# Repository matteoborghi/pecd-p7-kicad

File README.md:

# PECD P7: SiC traction inverter board (KiCad)

KiCad project of the board behind the report
[pecd-p7-report](https://github.com/matteoborghi/pecd-p7-report): a
three-phase two-level SiC traction inverter, 800 V DC link, 30 A rms per
phase, 20 kHz. The board is 6 layers, 1.6 mm thick, revision 1.2.

The report covers only the power stage. On the PCB it is the area marked
with a dashed box and a name on layer `User.1`.

## Schematic

The root sheet `PECD_P7.kicad_sch` has six hierarchical sheets:

| Sheet | Content |
|---|---|
| `1_power_stage` | six SiC MOSFETs (E3M0016120K), DC-link capacitors, shunts, DC and phase terminals |
| `2_gate_drive` | isolated gate drivers |
| `3_phase_sense` | current and voltage measurement |
| `4_aux_supply` | auxiliary supplies |
| `5_control_if` | interface to the controller |
| `6_dclink_mgmt` | DC-link management |

`leg.kicad_sch` is the half-bridge used three times in the power stage.
`drv_channel.kicad_sch` and `sense_channel.kicad_sch` are the repeated
gate-drive and measurement channels.

## Libraries

Symbols, footprints and 3D shapes of the parts that are not in the KiCad
standard libraries are in `PECD_P7.kicad_sym`, `PECD_P7.pretty` and
`PECD_P7.3dshapes`. The notes on each library file (in Italian) are in
`librerie/NOTE_librerie.md`.

## Tags

- `pcb-v1.0`, `pcb-v1.1`, `pcb-v1.2`: board revisions.
- `exam-v1`: board with the power-stage box used by the report.

The default branch is `for-exam`, which adds the power-stage box to `main`.

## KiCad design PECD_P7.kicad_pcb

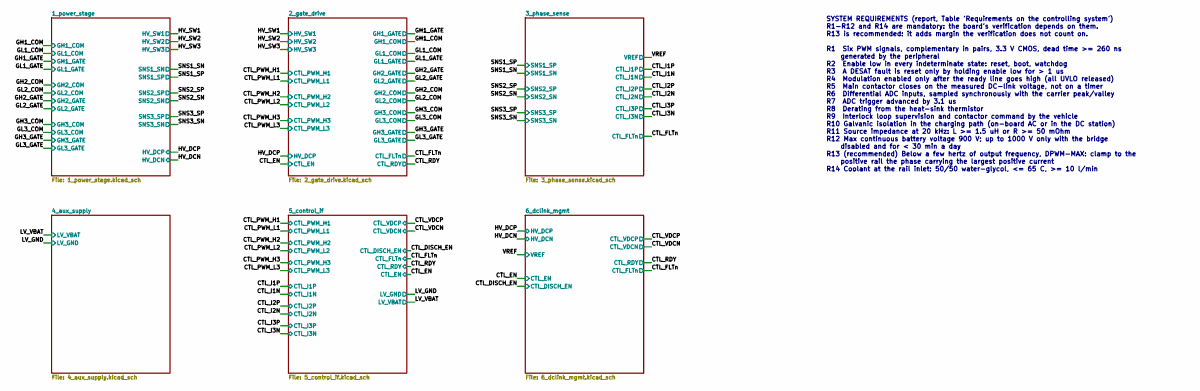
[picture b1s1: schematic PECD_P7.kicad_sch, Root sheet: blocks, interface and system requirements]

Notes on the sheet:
SYSTEM REQUIREMENTS (report, Table 'Requirements on the controlling system') R1-R12 and R14 are mandatory: the board's verification depends on them. R13 is recommended: it adds margin the verification does not count on. R1 Six PWM signals, complementary in pairs, 3.3 V CMOS, dead time >= 260 ns gen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

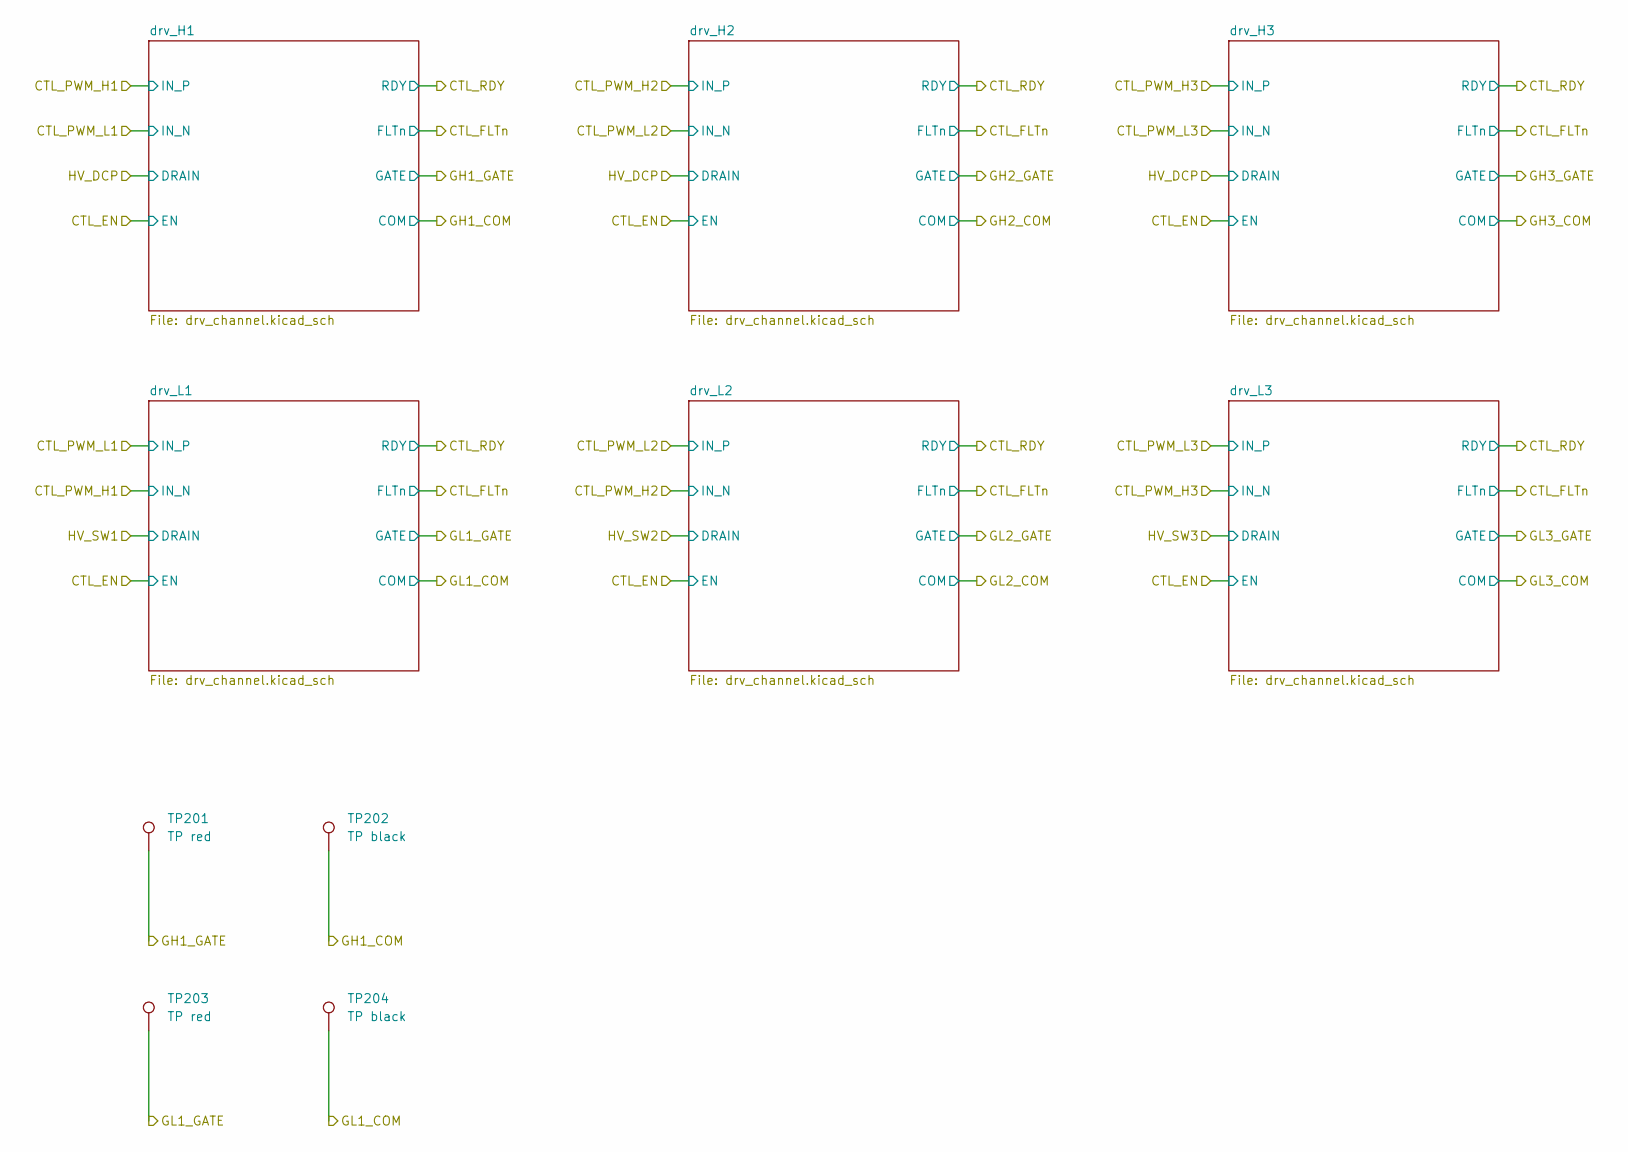
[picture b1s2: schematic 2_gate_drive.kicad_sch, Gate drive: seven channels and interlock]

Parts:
TP201, TP203: TP red; TestPoint_Keystone_5000-5004_Miniature; MPN 5000
TP202, TP204: TP black; TestPoint_Keystone_5000-5004_Miniature; MPN 5001

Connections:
/GH1_COM: TP202.1 (1_1); also elsewhere on the board
/GH1_GATE: TP201.1 (1_1); also elsewhere on the board
/GL1_COM: TP204.1 (1_1); also elsewhere on the board
/GL1_GATE: TP203.1 (1_1); also elsewhere on the board

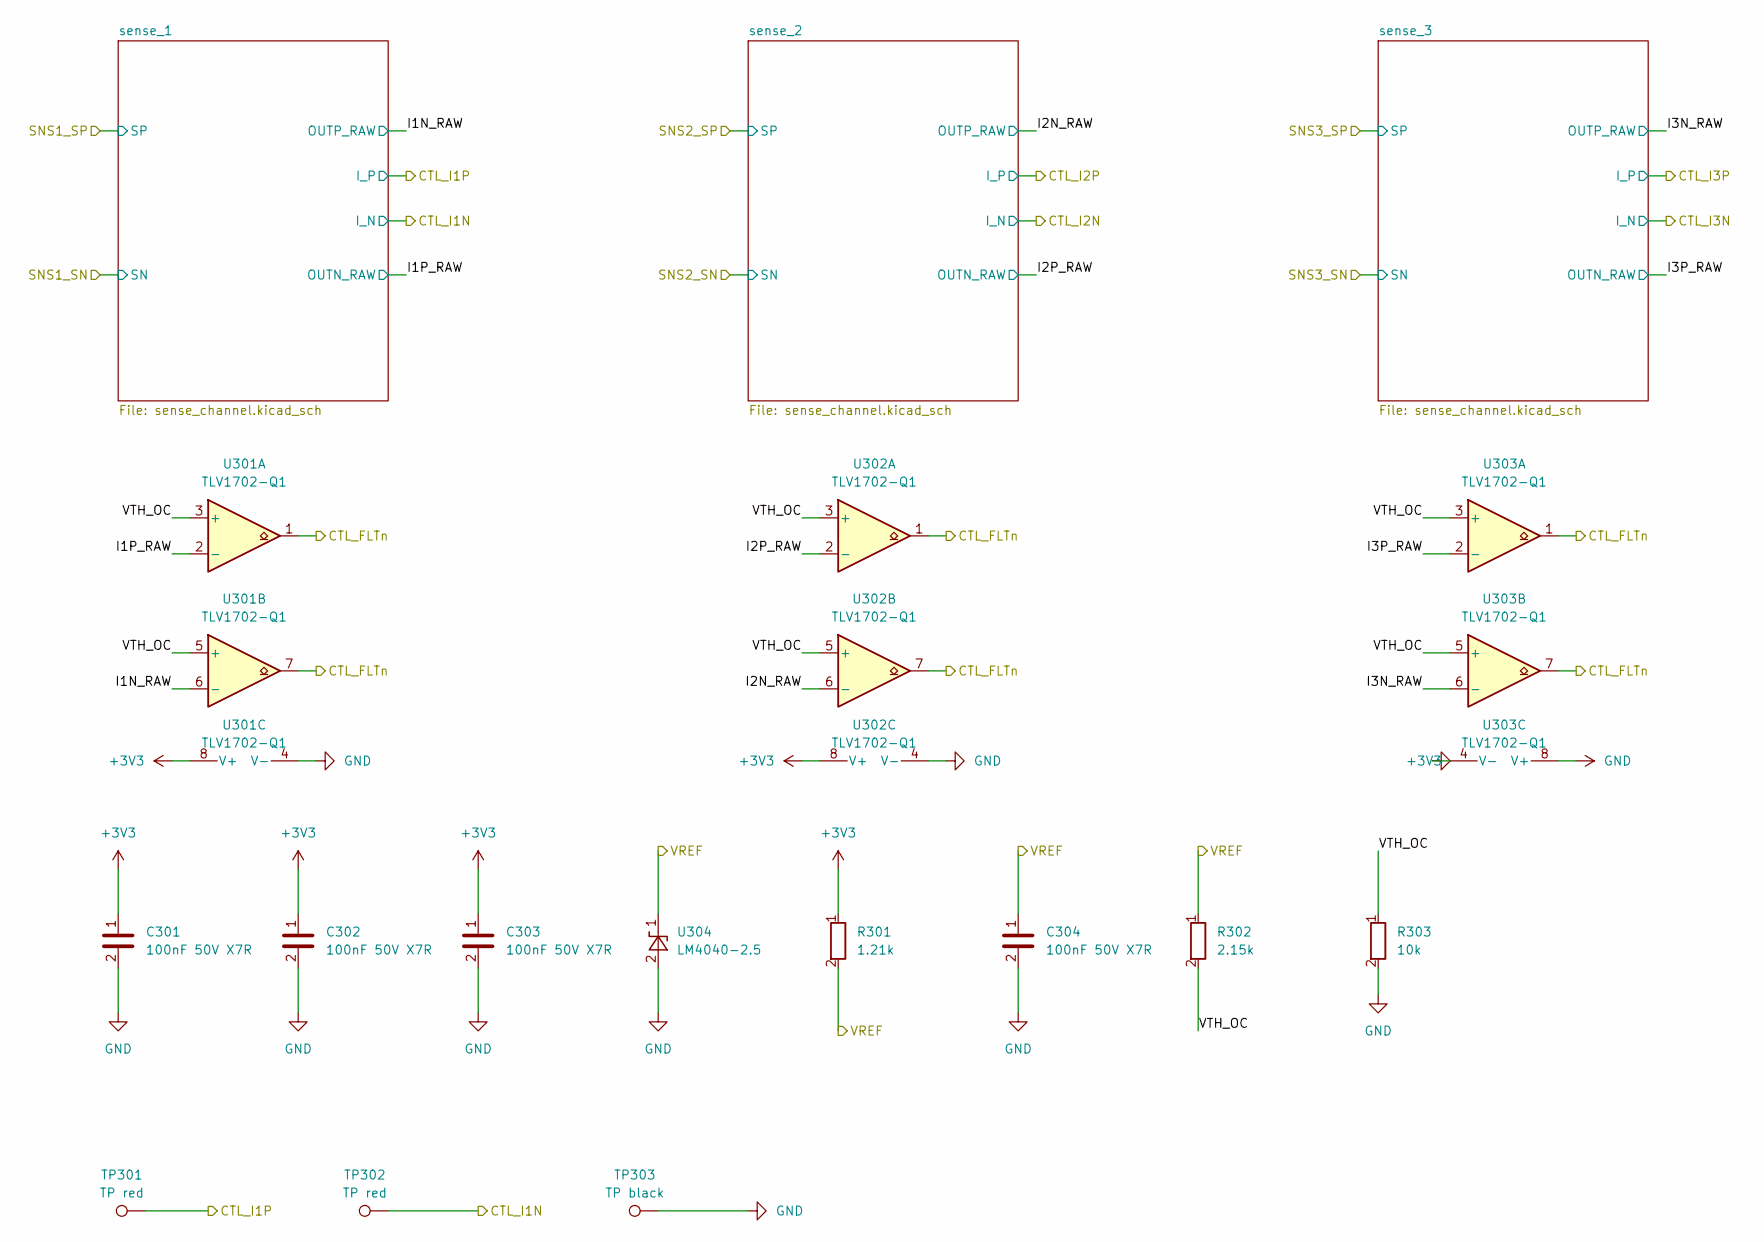
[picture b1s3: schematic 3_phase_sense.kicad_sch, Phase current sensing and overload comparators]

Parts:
C301, C302, C303, C304: 100nF 50V X7R; C_0603_1608Metric; MPN GCM188R71H104KA57D
R301: 1.21k; R_0603_1608Metric; MPN ERJ-3EKF1211V
R302: 2.15k; R_0603_1608Metric; MPN ERJ-3EKF2151V
R303: 10k; R_0603_1608Metric; MPN ERJ-3EKF1002V
TP301, TP302: TP red; TestPoint_Keystone_5000-5004_Miniature; MPN 5000
TP303: TP black; TestPoint_Keystone_5000-5004_Miniature; MPN 5001
U301, U302, U303: TLV1702-Q1; VSSOP-8_3x3mm_P0.65mm; MPN TLV1702AQDGKRQ1
U304: LM4040-2.5; SOT-23; MPN LM4040QBIM3-2.5/NOPB

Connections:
+3V3: C301.1, C302.1, C303.1, R301.1, U301.8 (V+), U302.8 (V+), U303.8 (V+); also elsewhere on the board
/3_phase_sense/I1N_RAW: U301.6 (-); also elsewhere on the board
/3_phase_sense/I1P_RAW: U301.2 (-); also elsewhere on the board
/3_phase_sense/I2N_RAW: U302.6 (-); also elsewhere on the board
/3_phase_sense/I2P_RAW: U302.2 (-); also elsewhere on the board
/3_phase_sense/I3N_RAW: U303.6 (-); also elsewhere on the board
/3_phase_sense/I3P_RAW: U303.2 (-); also elsewhere on the board
/3_phase_sense/VTH_OC: R302.2, R303.1, U301.3 (+), U301.5 (+), U302.3 (+), U302.5 (+), U303.3 (+), U303.5 (+)
/CTL_FLTn: U301.1, U301.7, U302.1, U302.7, U303.1, U303.7; also elsewhere on the board
/CTL_I1N: TP302.1 (1_1); also elsewhere on the board
/CTL_I1P: TP301.1 (1_1); also elsewhere on the board
/VREF: C304.1, R301.2, R302.1, U304.1 (K); also elsewhere on the board
GND: C301.2, C302.2, C303.2, C304.2, R303.2, TP303.1 (1_1), U301.4 (V-), U302.4 (V-), U303.4 (V-), U304.2 (A); also elsewhere on the board

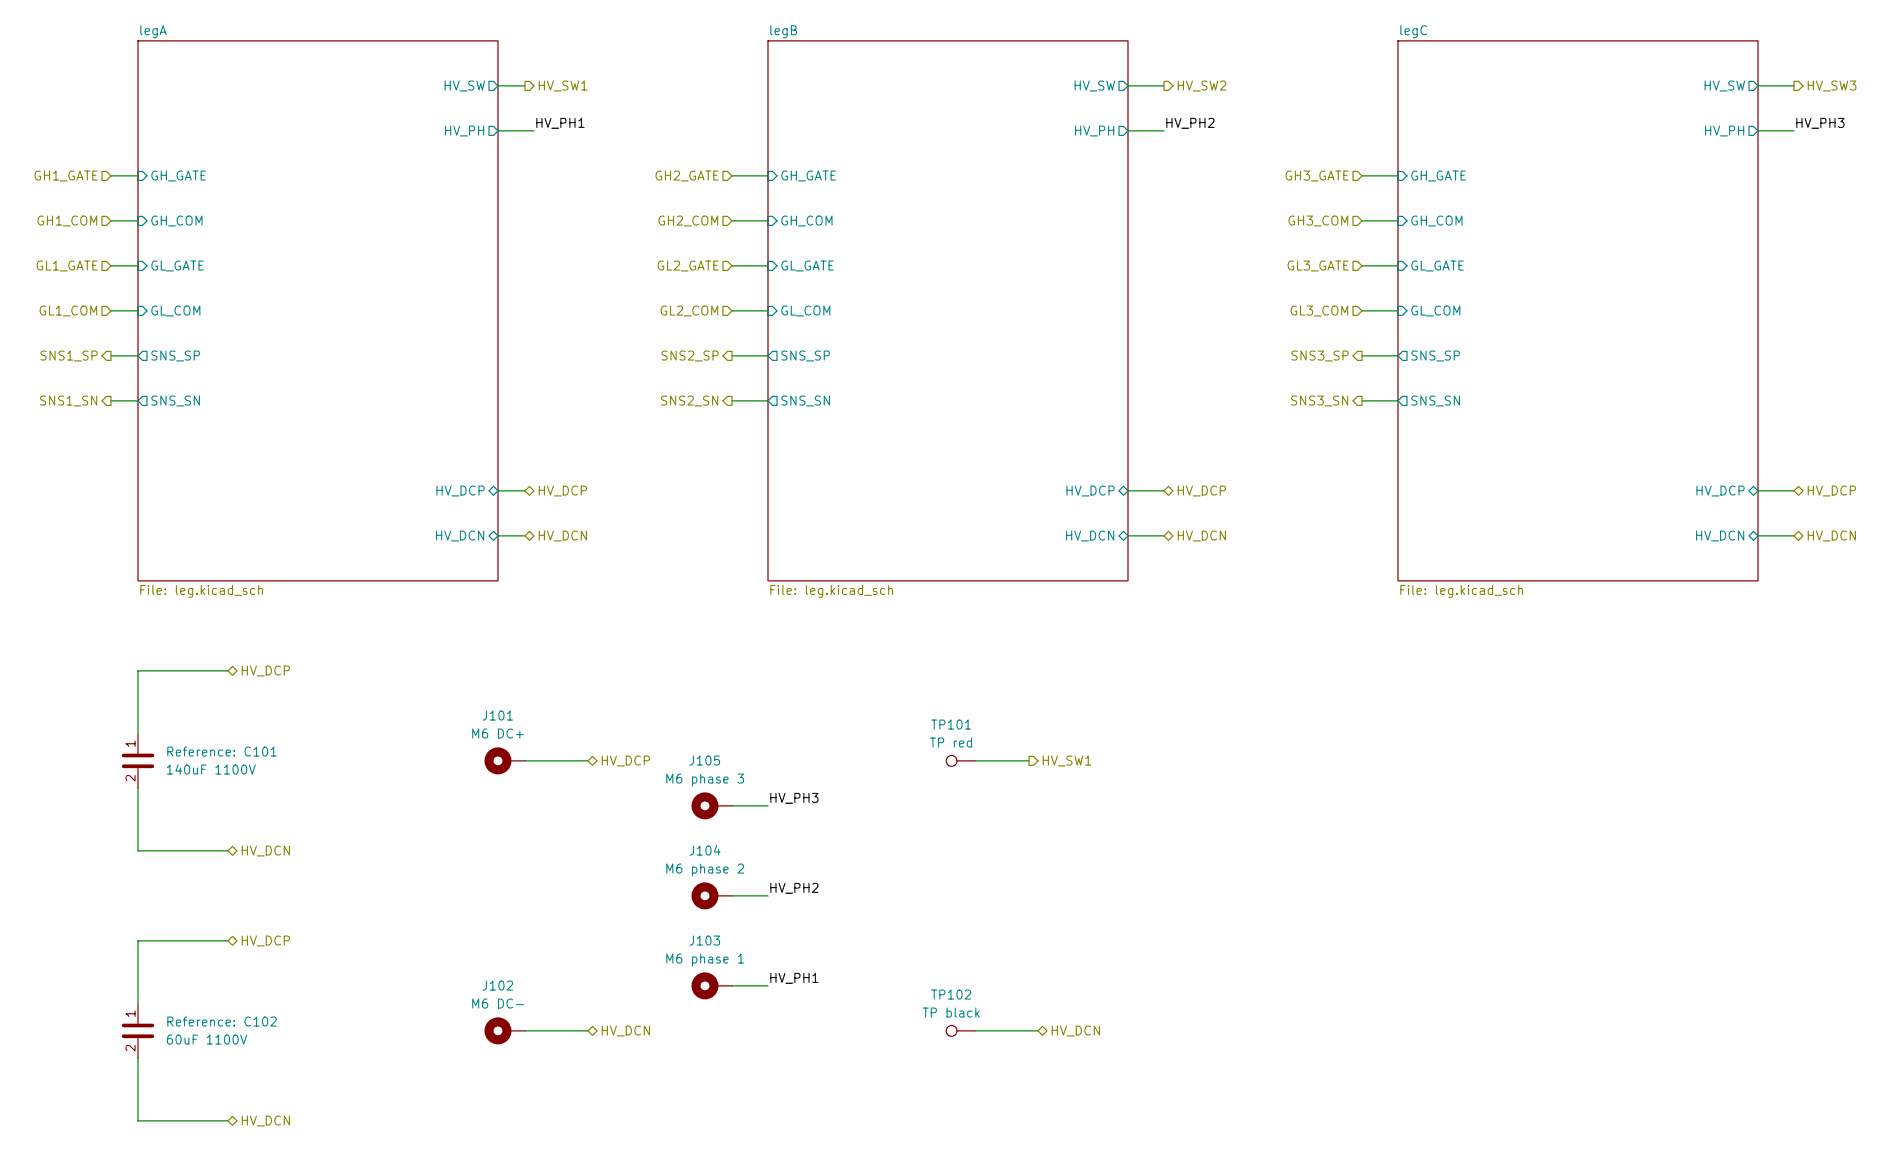
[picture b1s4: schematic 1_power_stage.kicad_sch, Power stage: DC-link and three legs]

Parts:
C101: 140uF 1100V; MKP1848_12pin_P52.5mm; MPN MKP1848714914Y5
C102: 60uF 1100V; MKP1848_6pin_P52.5mm; MPN MKP1848660914Y5
J101: M6 DC+; MountingHole_6.4mm_M6_Pad_Via
J102: M6 DC-; MountingHole_6.4mm_M6_Pad_Via
J103: M6 phase 1; MountingHole_6.4mm_M6_Pad_Via
J104: M6 phase 2; MountingHole_6.4mm_M6_Pad_Via
J105: M6 phase 3; MountingHole_6.4mm_M6_Pad_Via
TP101: TP red; TestPoint_Keystone_5000-5004_Miniature; MPN 5000
TP102: TP black; TestPoint_Keystone_5000-5004_Miniature; MPN 5001

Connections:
/1_power_stage/HV_PH1: J103.1 (1_1); also elsewhere on the board
/1_power_stage/HV_PH2: J104.1 (1_1); also elsewhere on the board
/1_power_stage/HV_PH3: J105.1 (1_1); also elsewhere on the board
/HV_DCN: C101.2, C102.2, J102.1 (1_1), TP102.1 (1_1); also elsewhere on the board
/HV_DCP: C101.1, C102.1, J101.1 (1_1); also elsewhere on the board
/HV_SW1: TP101.1 (1_1); also elsewhere on the board

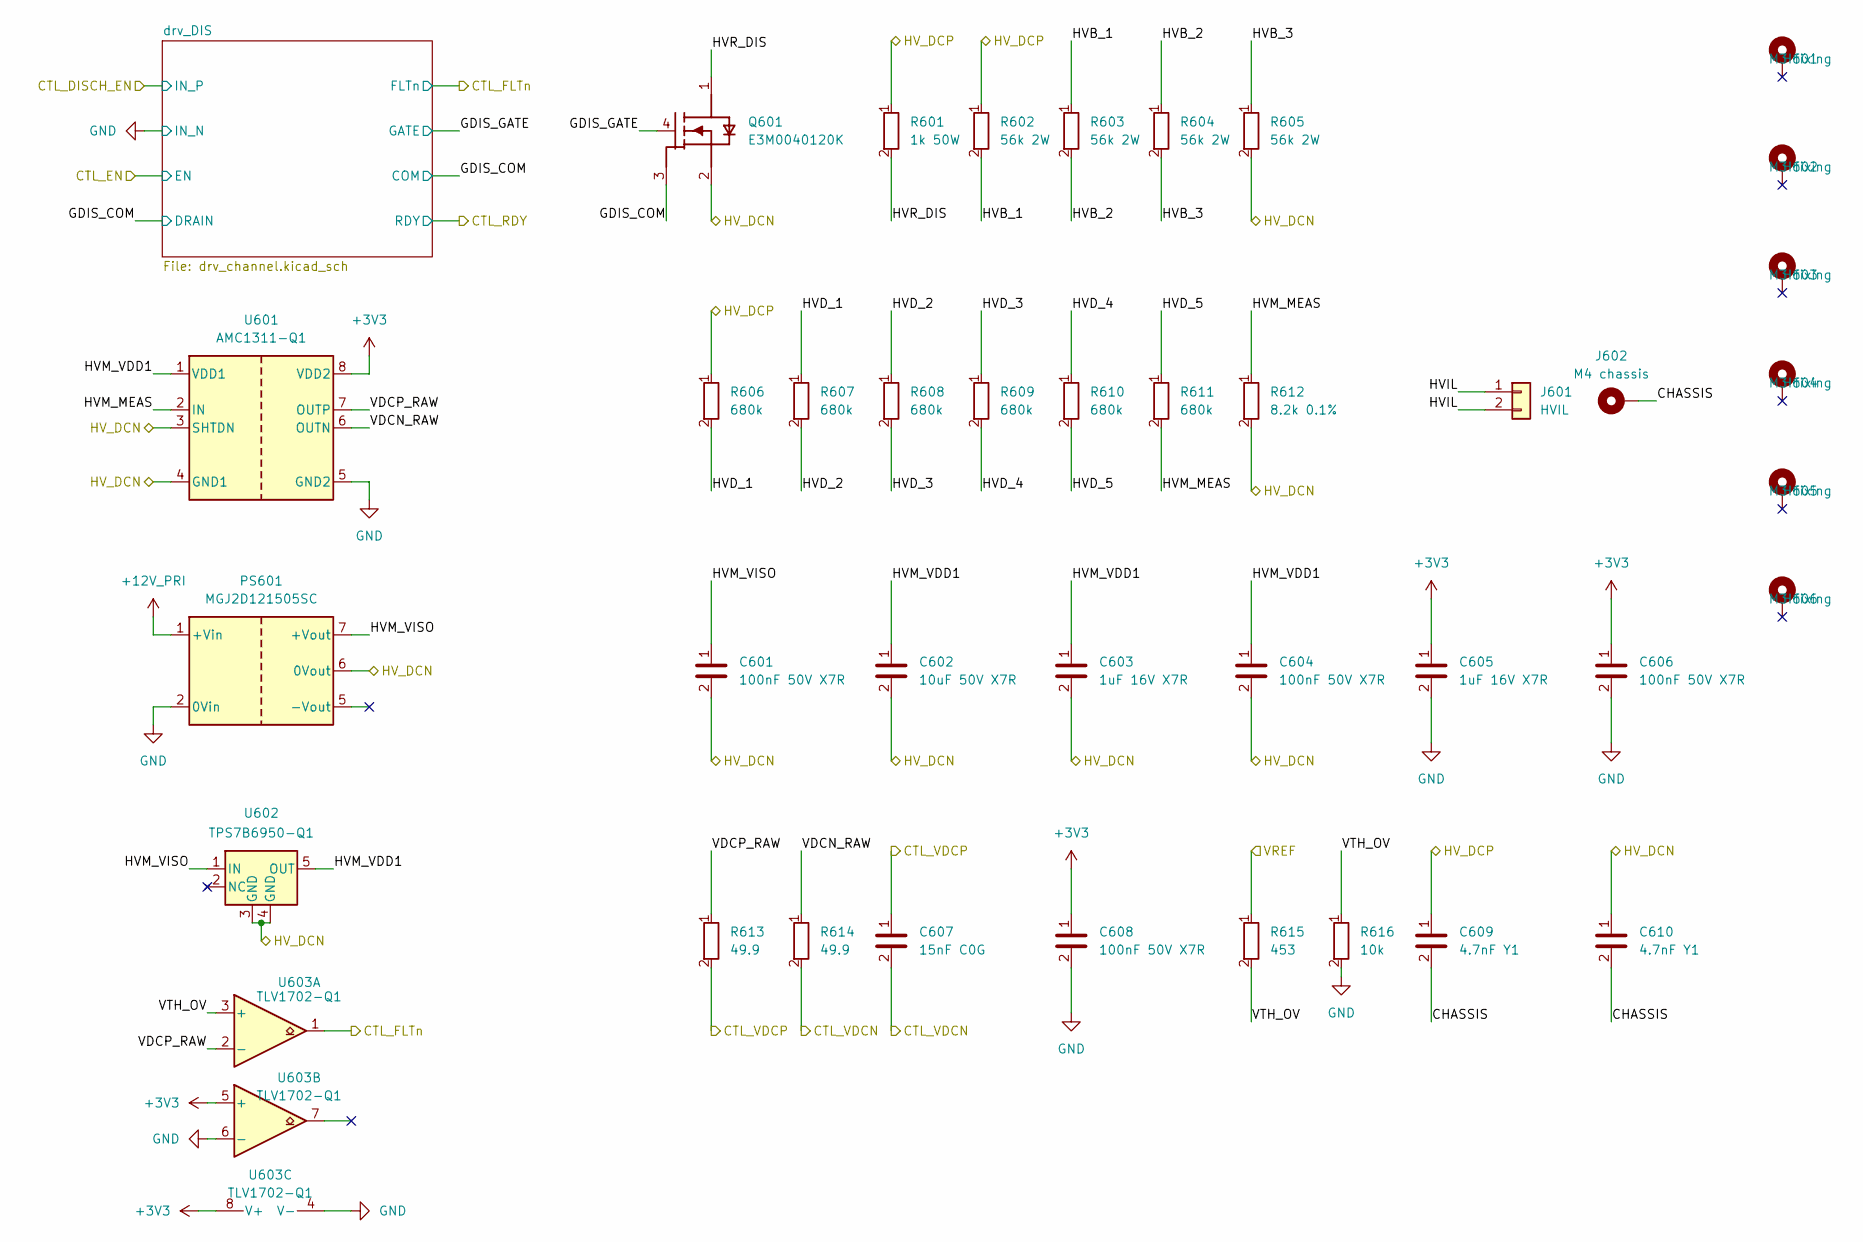
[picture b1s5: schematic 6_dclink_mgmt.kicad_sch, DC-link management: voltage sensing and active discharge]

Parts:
C601, C604, C606, C608: 100nF 50V X7R; C_0603_1608Metric; MPN GCM188R71H104KA57D
C602: 10uF 50V X7R; C_1210_3225Metric; MPN GRM32ER71H106KA12L
C603, C605: 1uF 16V X7R; C_0603_1608Metric; MPN GCM188R71C105KA64D
C607: 15nF C0G; C_0805_2012Metric; MPN GCM2195C1H153JA16D
C609, C610: 4.7nF Y1; C_Disc_Y1_D16.5_P12.5mm; MPN AY1472M65Y5UC63LX
H601, H602, H603, H604, H605, H606: M3 fixing; MountingHole_3.2mm_M3_Pad_Via
J601: HVIL; PhoenixContact_MSTBA_2,5_2-G-5,08_1x02_P5.08mm_Horizontal; MPN 1757242
J602: M4 chassis; MountingHole_4.3mm_M4_Pad_Via
PS601: MGJ2D121505SC; MGJ2_SIP7; MPN MGJ2D121505SC
Q601: E3M0040120K; TO-247-4L_Wolfspeed_Vertical; MPN E3M0040120K
R601: 1k 50W; Wire_HV_2x_P10mm; MPN HS50 1K J
R602, R603, R604, R605: 56k 2W; R_Axial_DIN0411_L9.9mm_D3.6mm_P15.24mm_Horizontal; MPN PR02000205602JR500
R606, R607, R608, R609, R610, R611: 680k; R_1206_3216Metric; MPN ERJ-8ENF6803V
R612: 8.2k 0.1%; R_1206_3216Metric; MPN ERA-3AEB822V
R613, R614: 49.9; R_0603_1608Metric; MPN ERJ-3EKF49R9V
R615: 453; R_0603_1608Metric; MPN ERJ-3EKF4530V
R616: 10k; R_0603_1608Metric; MPN ERJ-3EKF1002V
U601: AMC1311-Q1; SOIC-8W_TI_DWV_Slot; MPN AMC1311QDWVRQ1
U602: TPS7B6950-Q1; SOT-23-5; MPN TPS7B6950QDBVRQ1
U603: TLV1702-Q1; VSSOP-8_3x3mm_P0.65mm; MPN TLV1702AQDGKRQ1

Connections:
+3V3: C605.1, C606.1, C608.1, U601.8 (VDD2), U603.5 (+), U603.8 (V+); also elsewhere on the board
+12V_PRI: PS601.1 (+Vin); also elsewhere on the board
/6_dclink_mgmt/CHASSIS: C609.2, C610.2, J602.1 (1_1)
/6_dclink_mgmt/GDIS_COM: Q601.3 (S_K); also elsewhere on the board
/6_dclink_mgmt/GDIS_GATE: Q601.4 (G); also elsewhere on the board
/6_dclink_mgmt/HVB_1: R602.2, R603.1
/6_dclink_mgmt/HVB_2: R603.2, R604.1
/6_dclink_mgmt/HVB_3: R604.2, R605.1
/6_dclink_mgmt/HVD_1: R606.2, R607.1
/6_dclink_mgmt/HVD_2: R607.2, R608.1
/6_dclink_mgmt/HVD_3: R608.2, R609.1
/6_dclink_mgmt/HVD_4: R609.2, R610.1
/6_dclink_mgmt/HVD_5: R610.2, R611.1
/6_dclink_mgmt/HVIL: J601.1, J601.2
/6_dclink_mgmt/HVM_MEAS: R611.2, R612.1, U601.2 (IN)
/6_dclink_mgmt/HVM_VDD1: C602.1, C603.1, C604.1, U601.1 (VDD1), U602.5 (OUT)
/6_dclink_mgmt/HVM_VISO: C601.1, PS601.7 (+Vout), U602.1 (IN)
/6_dclink_mgmt/HVR_DIS: Q601.1 (D), R601.2
/6_dclink_mgmt/VDCN_RAW: R614.1, U601.6 (OUTN)
/6_dclink_mgmt/VDCP_RAW: R613.1, U601.7 (OUTP), U603.2 (-)
/6_dclink_mgmt/VTH_OV: R615.2, R616.1, U603.3 (+)
/CTL_FLTn: U603.1; also elsewhere on the board
/CTL_VDCN: C607.2, R614.2; also elsewhere on the board
/CTL_VDCP: C607.1, R613.2; also elsewhere on the board
/HV_DCN: C601.2, C602.2, C603.2, C604.2, C610.1, PS601.6 (0Vout), Q601.2 (S), R605.2, R612.2, U601.3 (SHTDN), U601.4 (GND1), U602.3 (GND), U602.4 (GND); also elsewhere on the board
/HV_DCP: C609.1, R601.1, R602.1, R606.1; also elsewhere on the board
/VREF: R615.1; also elsewhere on the board
GND: C605.2, C606.2, C608.2, PS601.2 (0Vin), R616.2, U601.5 (GND2), U603.4 (V-), U603.6 (-); also elsewhere on the board

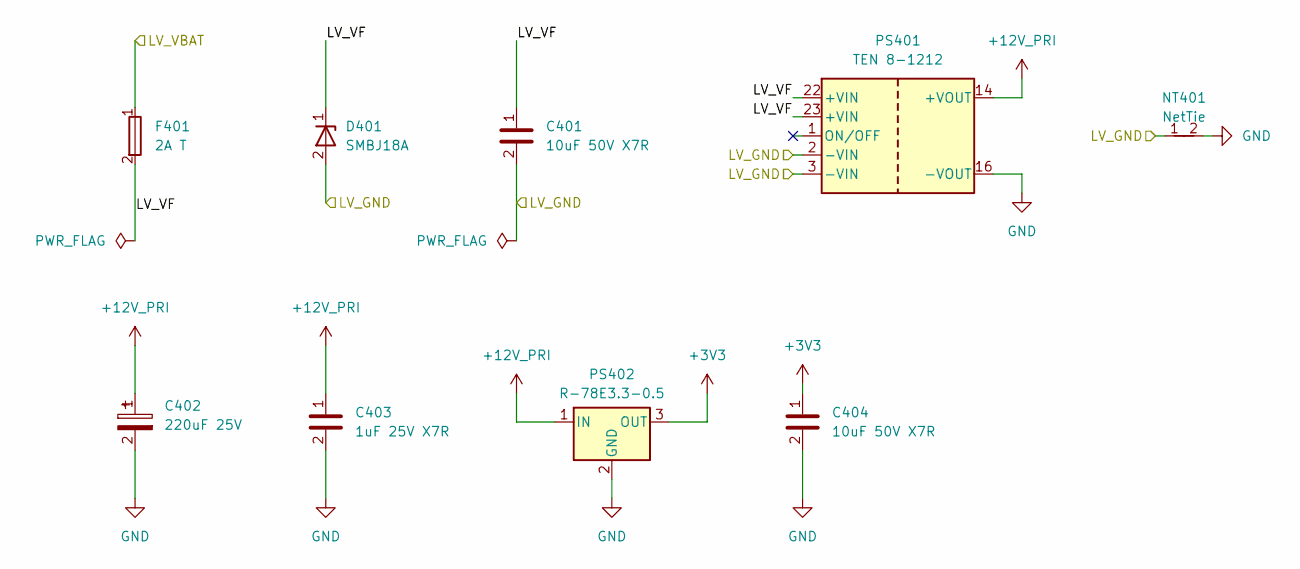
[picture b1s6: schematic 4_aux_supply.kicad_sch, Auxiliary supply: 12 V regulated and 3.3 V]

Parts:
C401, C404: 10uF 50V X7R; C_1210_3225Metric; MPN GRM32ER71H106KA12L
C402: 220uF 25V; CP_Elec_8x10.5; MPN EEE-FK1E221P
C403: 1uF 25V X7R; C_0603_1608Metric; MPN GCM188R71E105KA64D
D401: SMBJ18A; D_SMB; MPN SMBJ18A
F401: 2A T; Fuse_Littelfuse-NANO2-451_453; MPN 0452002.MRL
NT401: NetTie; NetTie-2_SMD_Pad0.5mm
PS401: TEN 8-1212; DIP-24_W15.24mm; MPN TEN 8-1212
PS402: R-78E3.3-0.5; Converter_DCDC_RECOM_R-78E-0.5_THT; MPN R-78E3.3-0.5

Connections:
+3V3: C404.1, PS402.3 (OUT); also elsewhere on the board
+12V_PRI: C402.1, C403.1, PS401.14 (+VOUT), PS402.1 (IN); also elsewhere on the board
/4_aux_supply/LV_VF: C401.1, D401.1 (K), F401.2, PS401.22 (+VIN), PS401.23 (+VIN)
/LV_GND: C401.2, D401.2 (A), NT401.1, PS401.2 (-VIN), PS401.3 (-VIN); also elsewhere on the board
/LV_VBAT: F401.1; also elsewhere on the board
GND: C402.2, C403.2, C404.2, NT401.2, PS401.16 (-VOUT), PS402.2 (GND); also elsewhere on the board

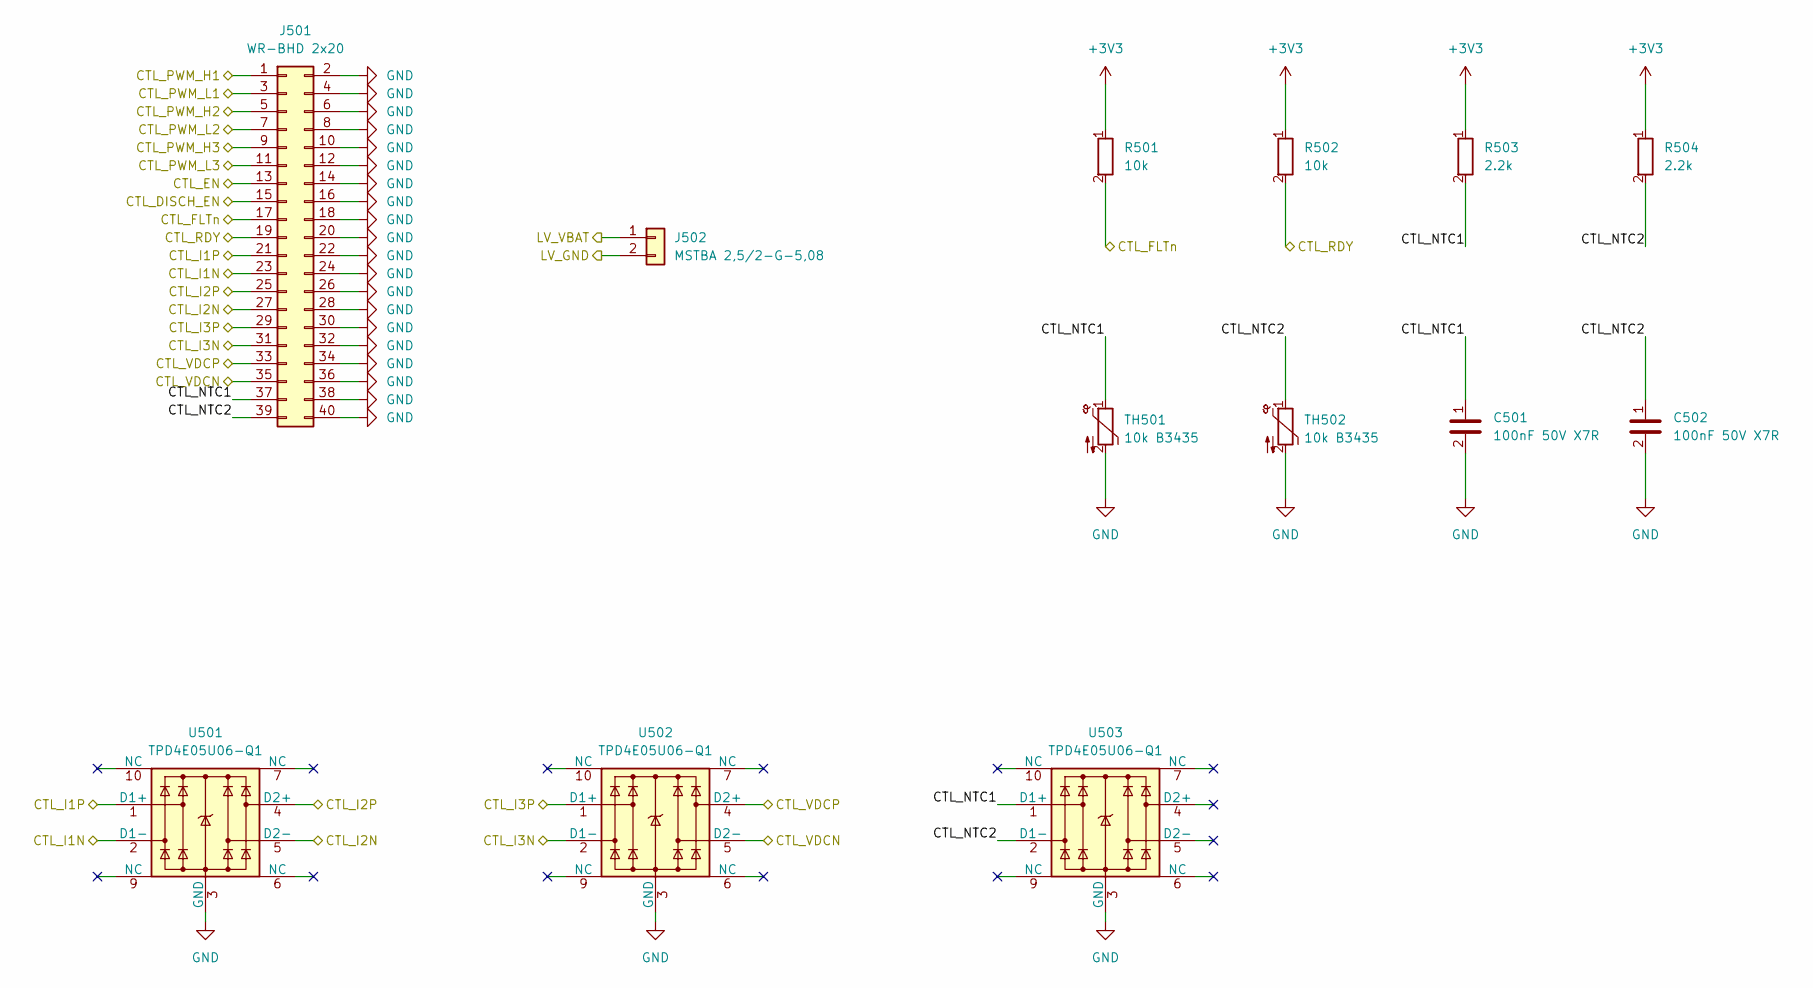
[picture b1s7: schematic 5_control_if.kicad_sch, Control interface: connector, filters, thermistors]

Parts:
C501, C502: 100nF 50V X7R; C_0603_1608Metric; MPN GCM188R71H104KA57D
J501: WR-BHD 2x20; IDC-Header_2x20_P2.54mm_Vertical; MPN 61204021621
J502: MSTBA 2,5/2-G-5,08; PhoenixContact_MSTBA_2,5_2-G-5,08_1x02_P5.08mm_Horizontal; MPN 1757242
R501, R502: 10k; R_0603_1608Metric; MPN ERJ-3EKF1002V
R503, R504: 2.2k; R_0603_1608Metric; MPN ERJ-3EKF2201V
TH501, TH502: 10k B3435; SolderWire-0.1sqmm_1x02_P3.6mm_D0.4mm_OD1mm; MPN NTCALUG01T103FL
U501, U502, U503: TPD4E05U06-Q1; USON-10_2.5x1.0mm_P0.5mm; MPN TPD4E05U06QDQARQ1

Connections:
+3V3: R501.1, R502.1, R503.1, R504.1; also elsewhere on the board
/5_control_if/CTL_NTC1: C501.1, J501.37, R503.2, TH501.1, U503.1 (D1+)
/5_control_if/CTL_NTC2: C502.1, J501.39, R504.2, TH502.1, U503.2 (D1-)
/CTL_DISCH_EN: J501.15; also elsewhere on the board
/CTL_EN: J501.13; also elsewhere on the board
/CTL_FLTn: J501.17, R501.2; also elsewhere on the board
/CTL_I1N: J501.23, U501.2 (D1-); also elsewhere on the board
/CTL_I1P: J501.21, U501.1 (D1+); also elsewhere on the board
/CTL_I2N: J501.27, U501.5 (D2-); also elsewhere on the board
/CTL_I2P: J501.25, U501.4 (D2+); also elsewhere on the board
/CTL_I3N: J501.31, U502.2 (D1-); also elsewhere on the board
/CTL_I3P: J501.29, U502.1 (D1+); also elsewhere on the board
/CTL_PWM_H1: J501.1; also elsewhere on the board
/CTL_PWM_H2: J501.5; also elsewhere on the board
/CTL_PWM_H3: J501.9; also elsewhere on the board
/CTL_PWM_L1: J501.3; also elsewhere on the board
/CTL_PWM_L2: J501.7; also elsewhere on the board
/CTL_PWM_L3: J501.11; also elsewhere on the board
/CTL_RDY: J501.19, R502.2; also elsewhere on the board
/CTL_VDCN: J501.35, U502.5 (D2-); also elsewhere on the board
/CTL_VDCP: J501.33, U502.4 (D2+); also elsewhere on the board
/LV_GND: J502.2; also elsewhere on the board
/LV_VBAT: J502.1; also elsewhere on the board
GND: C501.2, C502.2, J501.2, J501.4, J501.6, J501.8, J501.10, J501.12, J501.14, J501.16, J501.18, J501.20, J501.22, J501.24, J501.26, J501.28, J501.30, J501.32, J501.34, J501.36, J501.38, J501.40, TH501.2, TH502.2, U501.3 (GND), U501.8 (GND), U502.3 (GND), U502.8 (GND), U503.3 (GND), U503.8 (GND); also elsewhere on the board
